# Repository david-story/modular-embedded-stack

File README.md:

# modular-embedded-stack

Credit card sized modular embedded stackable boards that was designed for fun for a microprocessor / 
microcontroller class. Base board is a microcontroller board that supports a thru-hole or smd PIC18F45K20 chip,
depending on which board you select. Daughter boards that are currently implemented have sensors and peripheals
that the user can interact with. 

The following is current included in the files:
- Board and schematic for thru-hole microcontroller
- Board and schematic for SMD microcontroller
- Board and schematic sensor daughter board

The following will be created in the future:
- Board and schematic for communication daughter board
- Other daughter boards and modules.

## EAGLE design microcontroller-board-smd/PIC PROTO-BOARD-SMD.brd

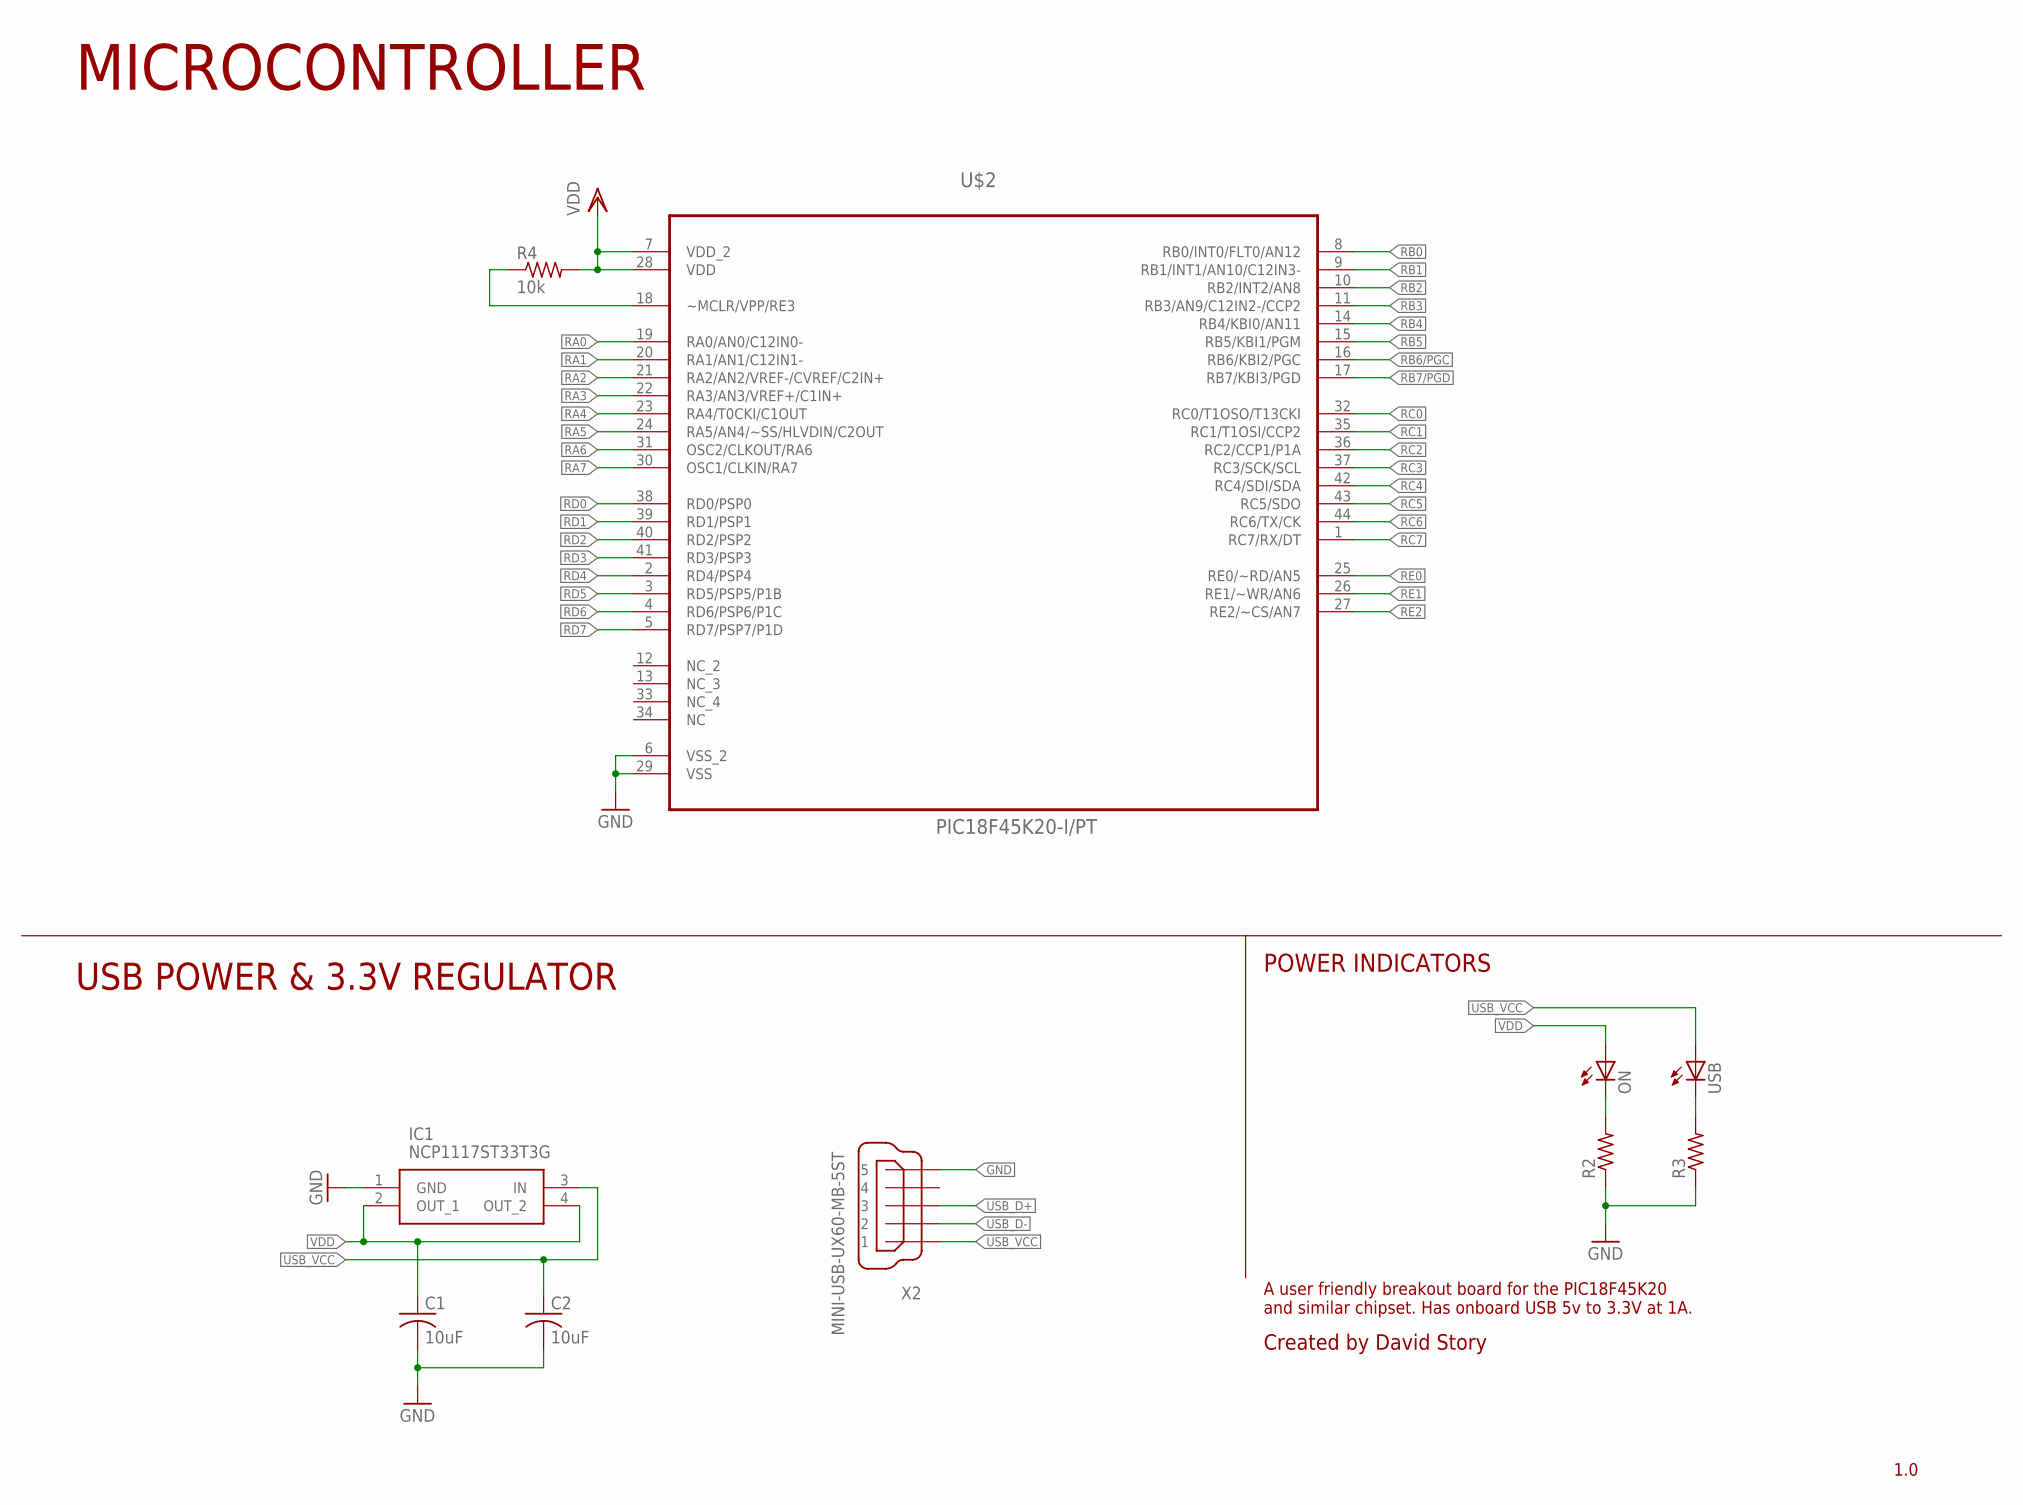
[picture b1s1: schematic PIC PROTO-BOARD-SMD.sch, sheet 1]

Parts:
C1, C2: 10uF; C0805
IC1: NCP1117ST33T3G; SOT230P700X180-4N
ON: LEDCHIP-LED0603; CHIP-LED0603
R2, R3: R-US_R0603; R0603
R4: 10k; R0805
U$2: PIC18F45K20-I/PT; QFP80P1200X1200X120-44N
USB: LEDCHIP-LED0603; CHIP-LED0603
X2: MINI-USB-UX60-MB-5ST; UX60-MB-5ST

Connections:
GND: C1.2, C2.2, IC1.1 (GND), R2.1, R3.1, U$2.6 (VSS_2), U$2.29 (VSS), X2.5; also elsewhere on the board
MCLR: R4.1, U$2.18 (~MCLR/VPP/RE3); also elsewhere on the board
ON_CATHODE: ON.C, R2.2
RA0: U$2.19 (RA0/AN0/C12IN0-); also elsewhere on the board
RA1: U$2.20 (RA1/AN1/C12IN1-); also elsewhere on the board
RA2: U$2.21 (RA2/AN2/VREF-/CVREF/C2IN+); also elsewhere on the board
RA3: U$2.22 (RA3/AN3/VREF+/C1IN+); also elsewhere on the board
RA4: U$2.23 (RA4/T0CKI/C1OUT); also elsewhere on the board
RA5: U$2.24 (RA5/AN4/~SS/HLVDIN/C2OUT); also elsewhere on the board
RA6: U$2.31 (OSC2/CLKOUT/RA6); also elsewhere on the board
RA7: U$2.30 (OSC1/CLKIN/RA7); also elsewhere on the board
RB0: U$2.8 (RB0/INT0/FLT0/AN12); also elsewhere on the board
RB1: U$2.9 (RB1/INT1/AN10/C12IN3-); also elsewhere on the board
RB2: U$2.10 (RB2/INT2/AN8); also elsewhere on the board
RB3: U$2.11 (RB3/AN9/C12IN2-/CCP2); also elsewhere on the board
RB4: U$2.14 (RB4/KBI0/AN11); also elsewhere on the board
RB5: U$2.15 (RB5/KBI1/PGM); also elsewhere on the board
RB6/PGC: U$2.16 (RB6/KBI2/PGC); also elsewhere on the board
RB7/PGD: U$2.17 (RB7/KBI3/PGD); also elsewhere on the board
RC0: U$2.32 (RC0/T1OSO/T13CKI); also elsewhere on the board
RC1: U$2.35 (RC1/T1OSI/CCP2); also elsewhere on the board
RC2: U$2.36 (RC2/CCP1/P1A); also elsewhere on the board
RC3: U$2.37 (RC3/SCK/SCL); also elsewhere on the board
RC4: U$2.42 (RC4/SDI/SDA); also elsewhere on the board
RC5: U$2.43 (RC5/SDO); also elsewhere on the board
RC6: U$2.44 (RC6/TX/CK); also elsewhere on the board
RC7: U$2.1 (RC7/RX/DT); also elsewhere on the board
RD0: U$2.38 (RD0/PSP0); also elsewhere on the board
RD1: U$2.39 (RD1/PSP1); also elsewhere on the board
RD2: U$2.40 (RD2/PSP2); also elsewhere on the board
RD3: U$2.41 (RD3/PSP3); also elsewhere on the board
RD4: U$2.2 (RD4/PSP4); also elsewhere on the board
RD5: U$2.3 (RD5/PSP5/P1B); also elsewhere on the board
RD6: U$2.4 (RD6/PSP6/P1C); also elsewhere on the board
RD7: U$2.5 (RD7/PSP7/P1D); also elsewhere on the board
RE0: U$2.25 (RE0/~RD/AN5); also elsewhere on the board
RE1: U$2.26 (RE1/~WR/AN6); also elsewhere on the board
RE2: U$2.27 (RE2/~CS/AN7); also elsewhere on the board
USB_CATHODE: R3.2, USB.C
USB_D+: X2.3; also elsewhere on the board
USB_D-: X2.2; also elsewhere on the board
USB_VCC: C2.1, IC1.3 (IN), USB.A, X2.1; also elsewhere on the board
VDD: C1.1, IC1.2 (OUT_1), IC1.4 (OUT_2), ON.A, R4.2, U$2.7 (VDD_2), U$2.28 (VDD); also elsewhere on the board

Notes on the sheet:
Created by David Story
1.0
MICROCONTROLLER
USB POWER & 3.3V REGULATOR
POWER INDICATORS
A user friendly breakout board for the PIC18F45K20 and similar chipset. Has onboard USB 5v to 3.3V at 1A.

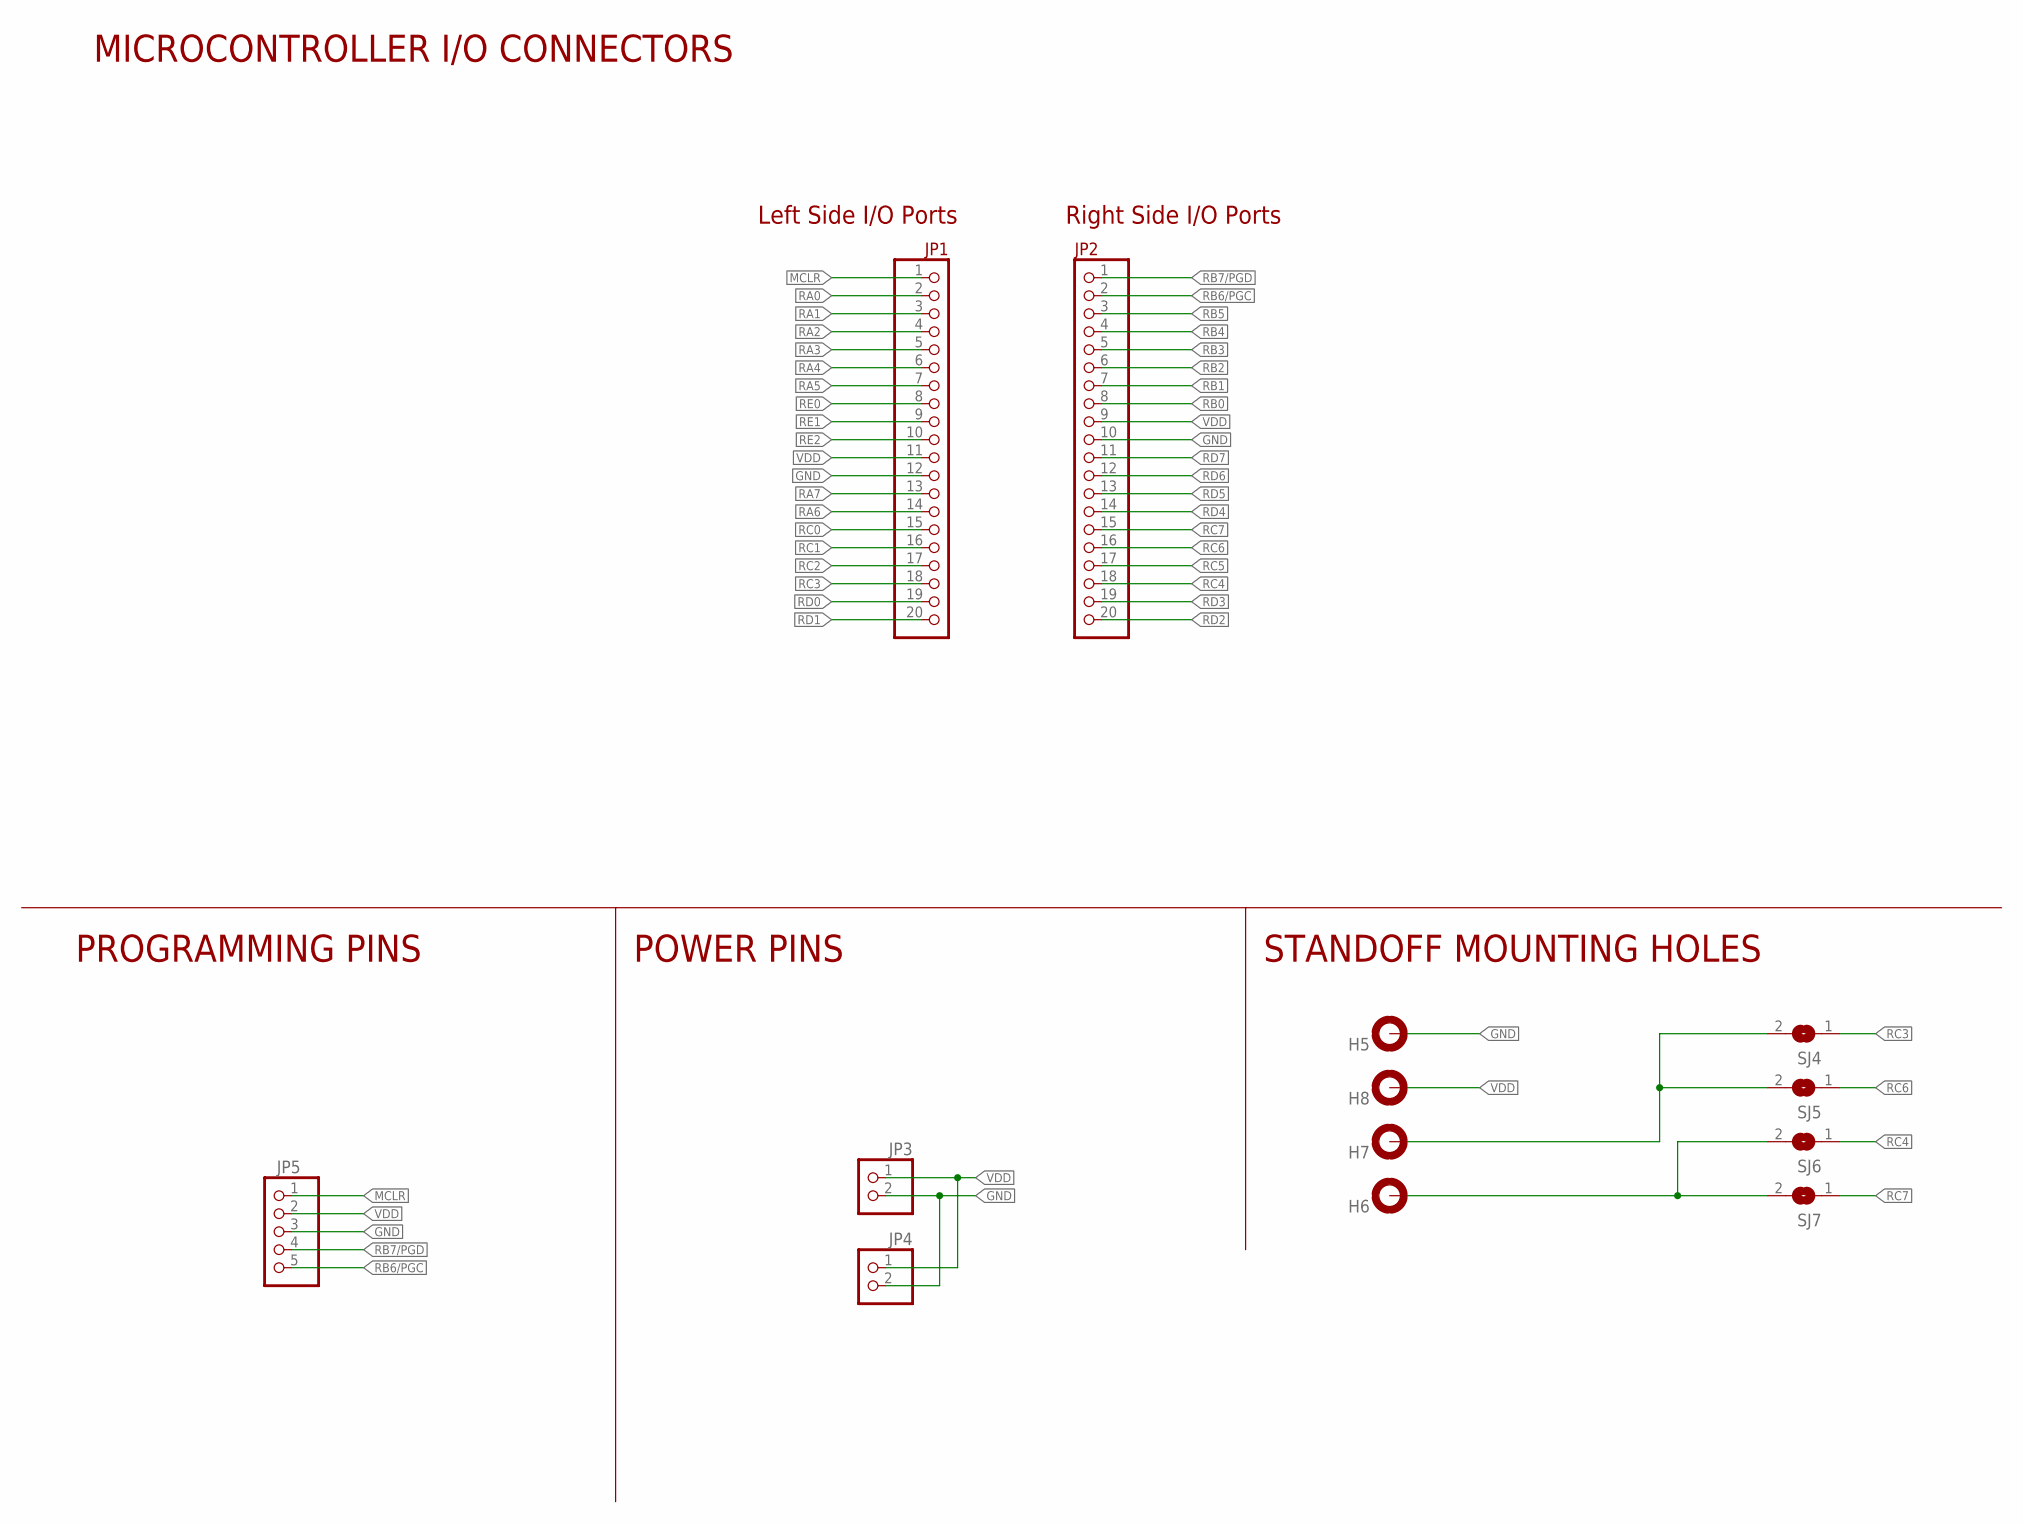
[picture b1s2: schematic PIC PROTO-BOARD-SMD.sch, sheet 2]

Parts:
H5, H6, H7, H8: MOUNT-PAD-ROUND3.3; 3,3-PAD
JP1, JP2: PINHD-1X20; 1X20
JP3, JP4: PINHD-1X2; 1X02
JP5: PINHD-1X5; 1X05
SJ4, SJ5, SJ6, SJ7: SJ

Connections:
COM_HOLE_1: H7.B3,3, SJ4.2, SJ5.2
COM_HOLE_2: H6.B3,3, SJ6.2, SJ7.2
GND: H5.B3,3, JP1.12, JP2.10, JP3.2, JP4.2, JP5.3; also elsewhere on the board
MCLR: JP1.1, JP5.1; also elsewhere on the board
RA0: JP1.2; also elsewhere on the board
RA1: JP1.3; also elsewhere on the board
RA2: JP1.4; also elsewhere on the board
RA3: JP1.5; also elsewhere on the board
RA4: JP1.6; also elsewhere on the board
RA5: JP1.7; also elsewhere on the board
RA6: JP1.14; also elsewhere on the board
RA7: JP1.13; also elsewhere on the board
RB0: JP2.8; also elsewhere on the board
RB1: JP2.7; also elsewhere on the board
RB2: JP2.6; also elsewhere on the board
RB3: JP2.5; also elsewhere on the board
RB4: JP2.4; also elsewhere on the board
RB5: JP2.3; also elsewhere on the board
RB6/PGC: JP2.2, JP5.5; also elsewhere on the board
RB7/PGD: JP2.1, JP5.4; also elsewhere on the board
RC0: JP1.15; also elsewhere on the board
RC1: JP1.16; also elsewhere on the board
RC2: JP1.17; also elsewhere on the board
RC3: JP1.18, SJ4.1; also elsewhere on the board
RC4: JP2.18, SJ6.1; also elsewhere on the board
RC5: JP2.17; also elsewhere on the board
RC6: JP2.16, SJ5.1; also elsewhere on the board
RC7: JP2.15, SJ7.1; also elsewhere on the board
RD0: JP1.19; also elsewhere on the board
RD1: JP1.20; also elsewhere on the board
RD2: JP2.20; also elsewhere on the board
RD3: JP2.19; also elsewhere on the board
RD4: JP2.14; also elsewhere on the board
RD5: JP2.13; also elsewhere on the board
RD6: JP2.12; also elsewhere on the board
RD7: JP2.11; also elsewhere on the board
RE0: JP1.8; also elsewhere on the board
RE1: JP1.9; also elsewhere on the board
RE2: JP1.10; also elsewhere on the board
VDD: H8.B3,3, JP1.11, JP2.9, JP3.1, JP4.1, JP5.2; also elsewhere on the board

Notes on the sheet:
Left Side I/O Ports
Right Side I/O Ports
PROGRAMMING PINS
POWER PINS
STANDOFF MOUNTING HOLES
MICROCONTROLLER I/O CONNECTORS

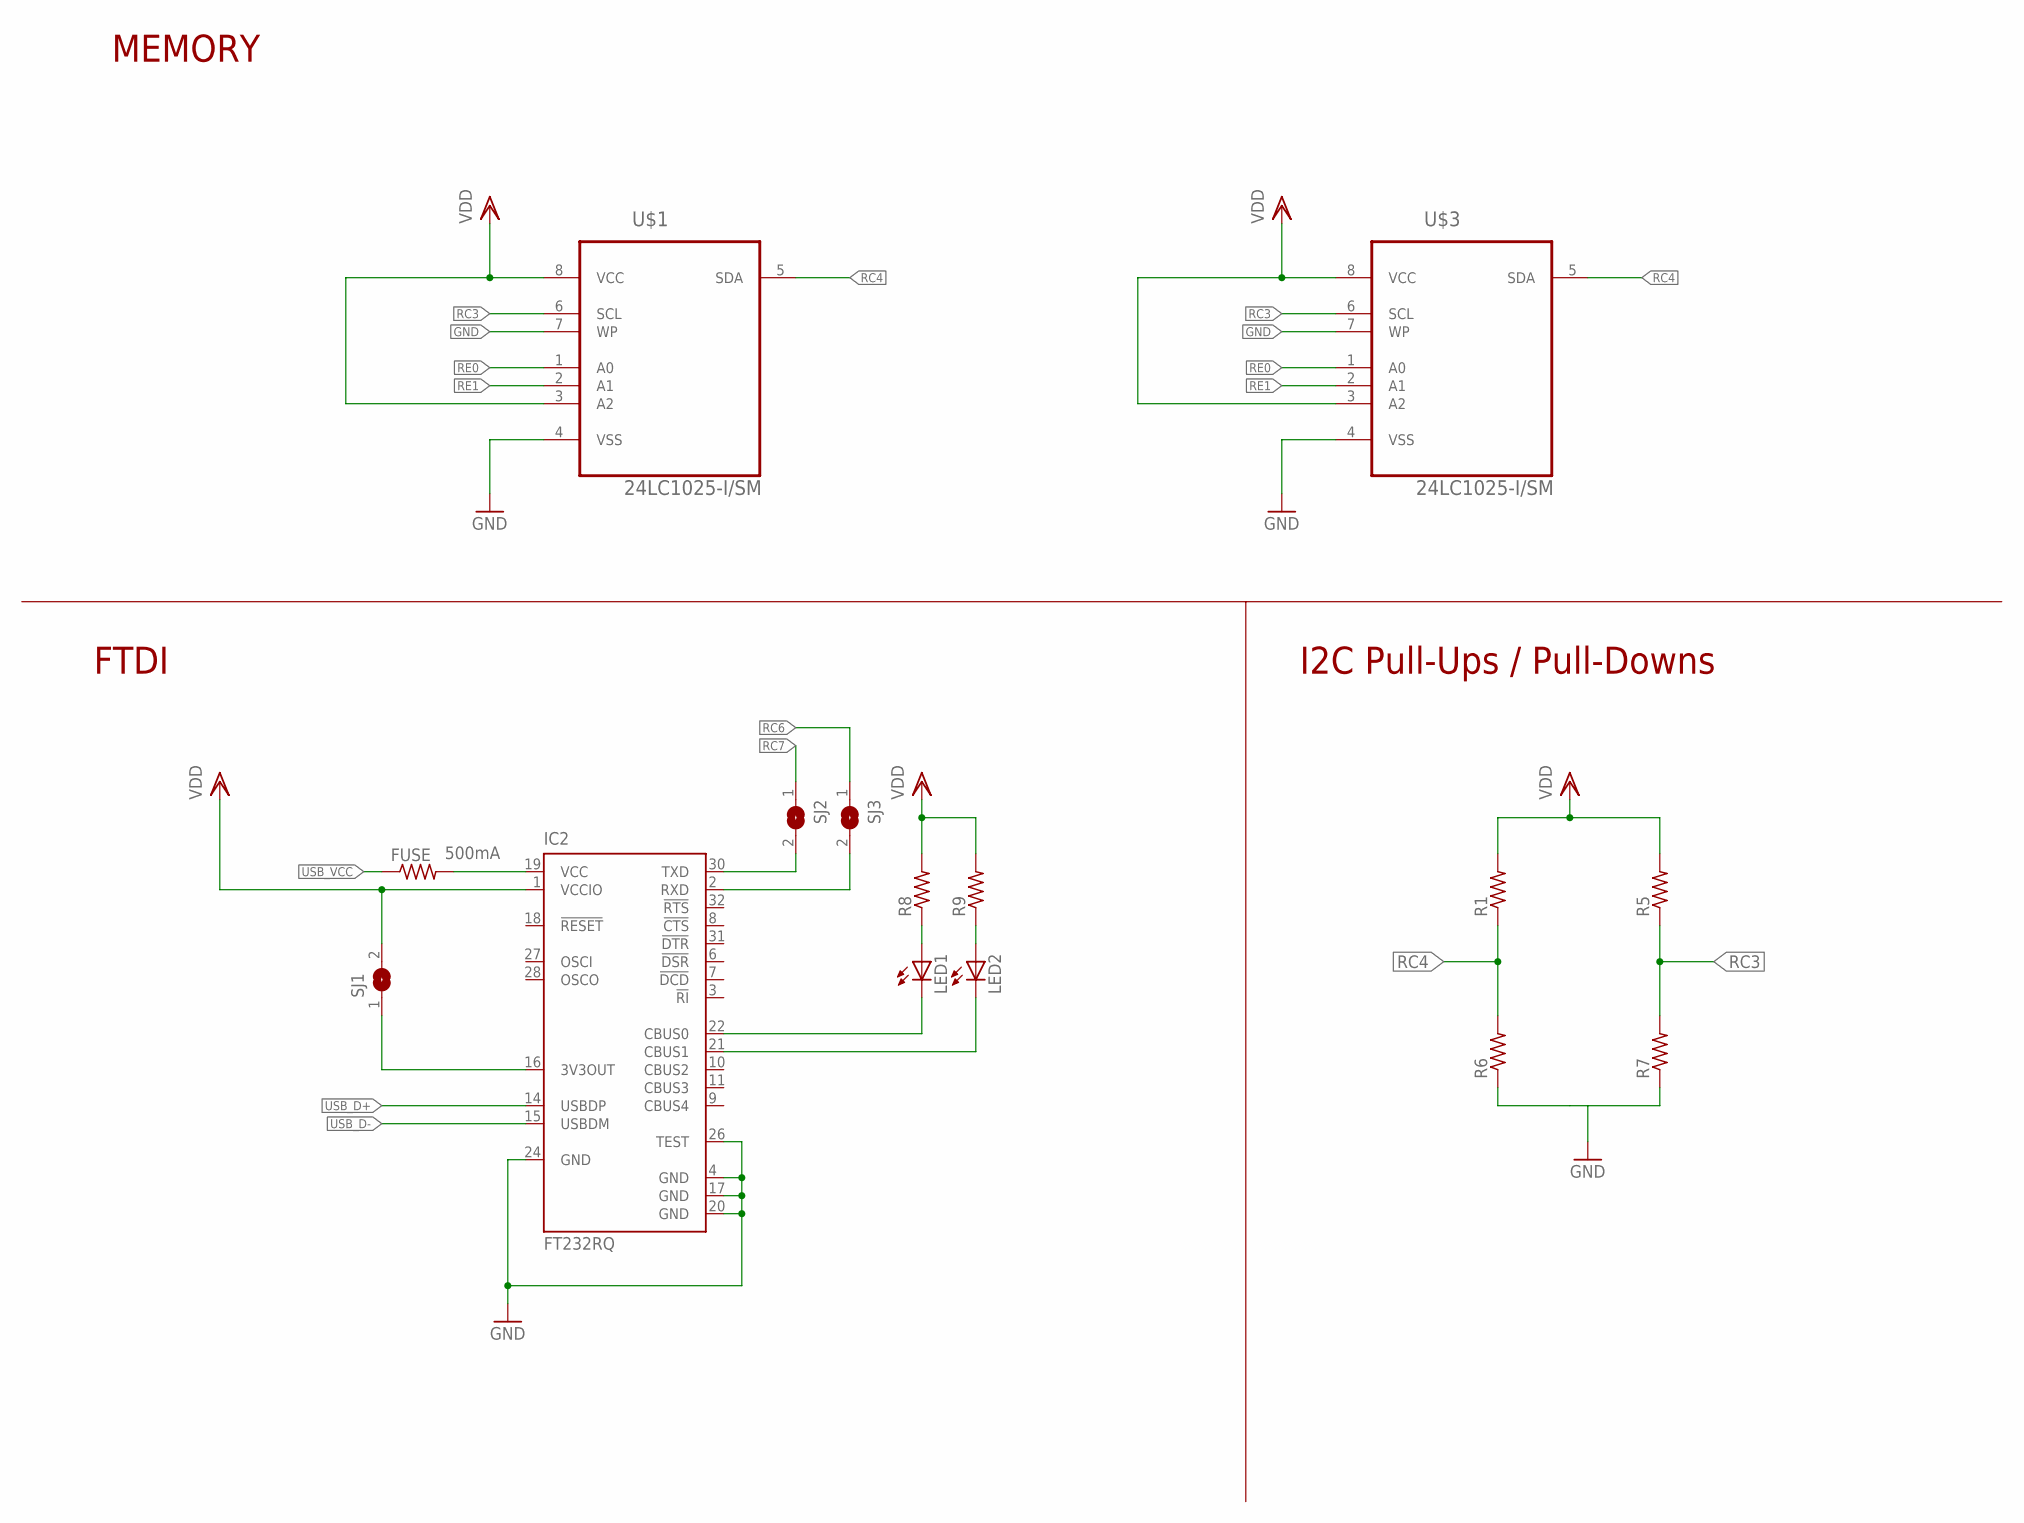
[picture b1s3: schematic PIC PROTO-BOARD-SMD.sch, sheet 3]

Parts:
FUSE: 500mA; M0805
IC2: FT232RQ; QFN32
LED1, LED2: LEDSML0603; SML0603
R1, R5, R6, R7, R8, R9: R-US_R0805; R0805
SJ1, SJ2, SJ3: SJ
U$1, U$3: 24LC1025-I/SM; SOIC127P794X203-8N

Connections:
3V3OUT: IC2.16 (3V3OUT), SJ1.1
FUSE_TO_FTDI: FUSE.2, IC2.19 (VCC)
GND: IC2.4 (GND), IC2.17 (GND), IC2.20 (GND), IC2.24 (GND), IC2.26 (TEST), R6.1, R7.1, U$1.4 (VSS), U$1.7 (WP), U$3.4 (VSS), U$3.7 (WP); also elsewhere on the board
LEDTX: LED1.A, R8.1
RC3: R5.1, R7.2, U$1.6 (SCL), U$3.6 (SCL); also elsewhere on the board
RC4: R1.1, R6.2, U$1.5 (SDA), U$3.5 (SDA); also elsewhere on the board
RC6: SJ3.1; also elsewhere on the board
RC7: SJ2.1; also elsewhere on the board
RE0: U$1.1 (A0), U$3.1 (A0); also elsewhere on the board
RE1: U$1.2 (A1), U$3.2 (A1); also elsewhere on the board
RXD: IC2.2 (RXD), SJ3.2
RXLED: LED2.A, R9.1
RX_LED: IC2.21 (CBUS1), LED2.C
TXD: IC2.30 (TXD), SJ2.2
TX_LED: IC2.22 (CBUS0), LED1.C
USB_D+: IC2.14 (USBDP); also elsewhere on the board
USB_D-: IC2.15 (USBDM); also elsewhere on the board
USB_VCC: FUSE.1; also elsewhere on the board
VDD: IC2.1 (VCCIO), R1.2, R5.2, R8.2, R9.2, SJ1.2, U$1.3 (A2), U$1.8 (VCC), U$3.3 (A2), U$3.8 (VCC); also elsewhere on the board

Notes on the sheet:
MEMORY
I2C Pull-Ups / Pull-Downs
FTDI

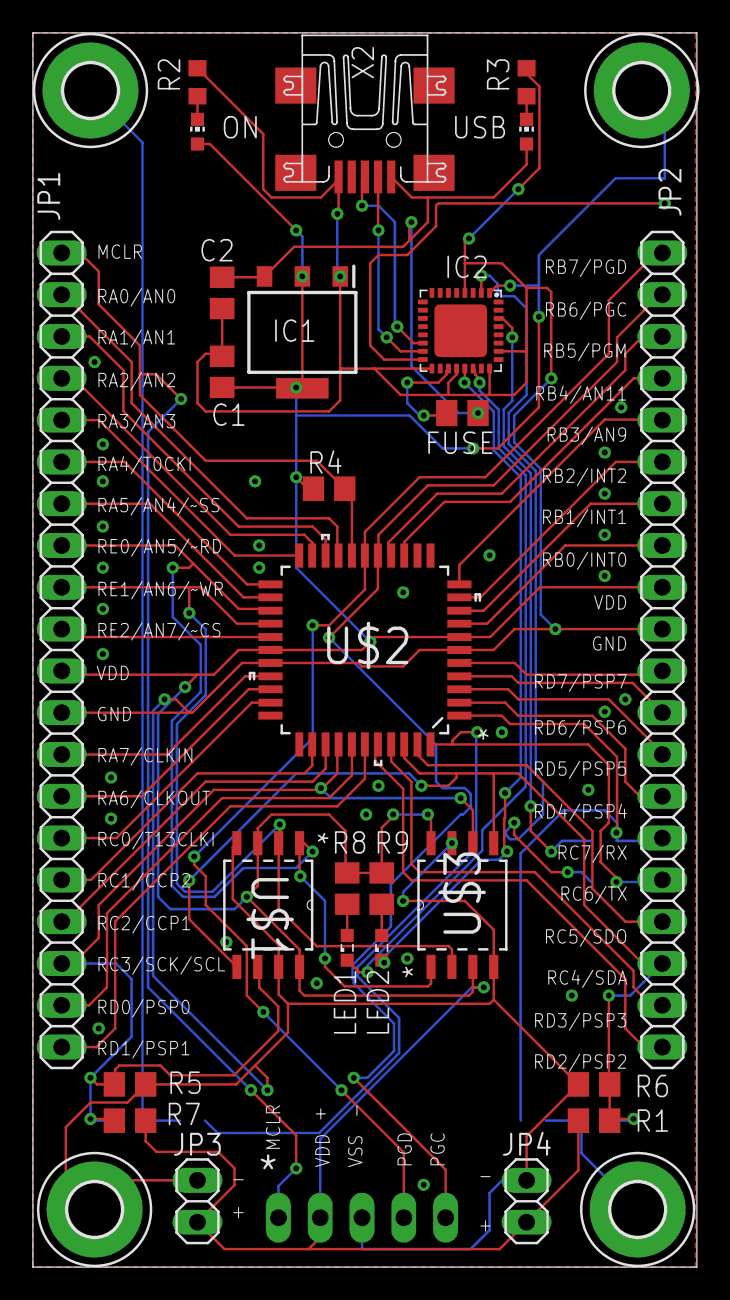
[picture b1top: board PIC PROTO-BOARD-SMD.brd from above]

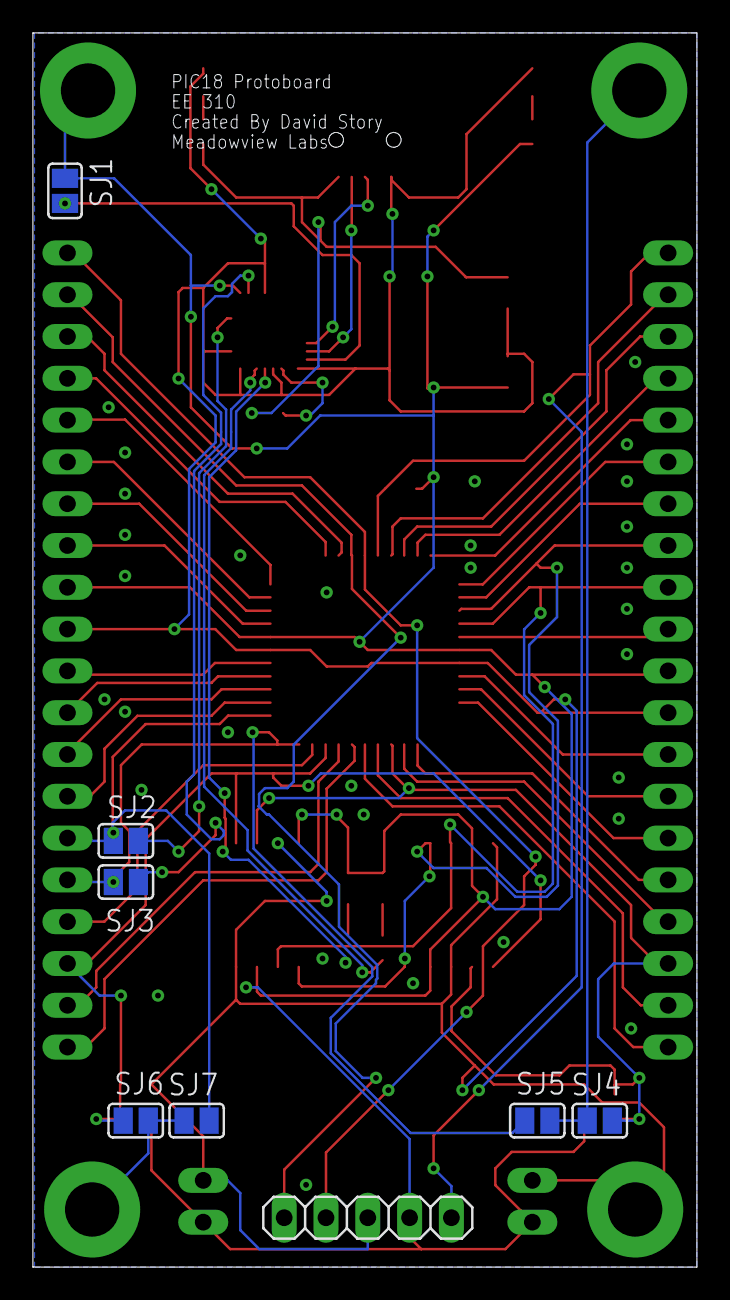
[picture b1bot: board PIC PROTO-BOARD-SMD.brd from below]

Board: 2 copper layers, 40.4 x 75.0 mm, 38 parts (8 on the bottom side), 53 nets.

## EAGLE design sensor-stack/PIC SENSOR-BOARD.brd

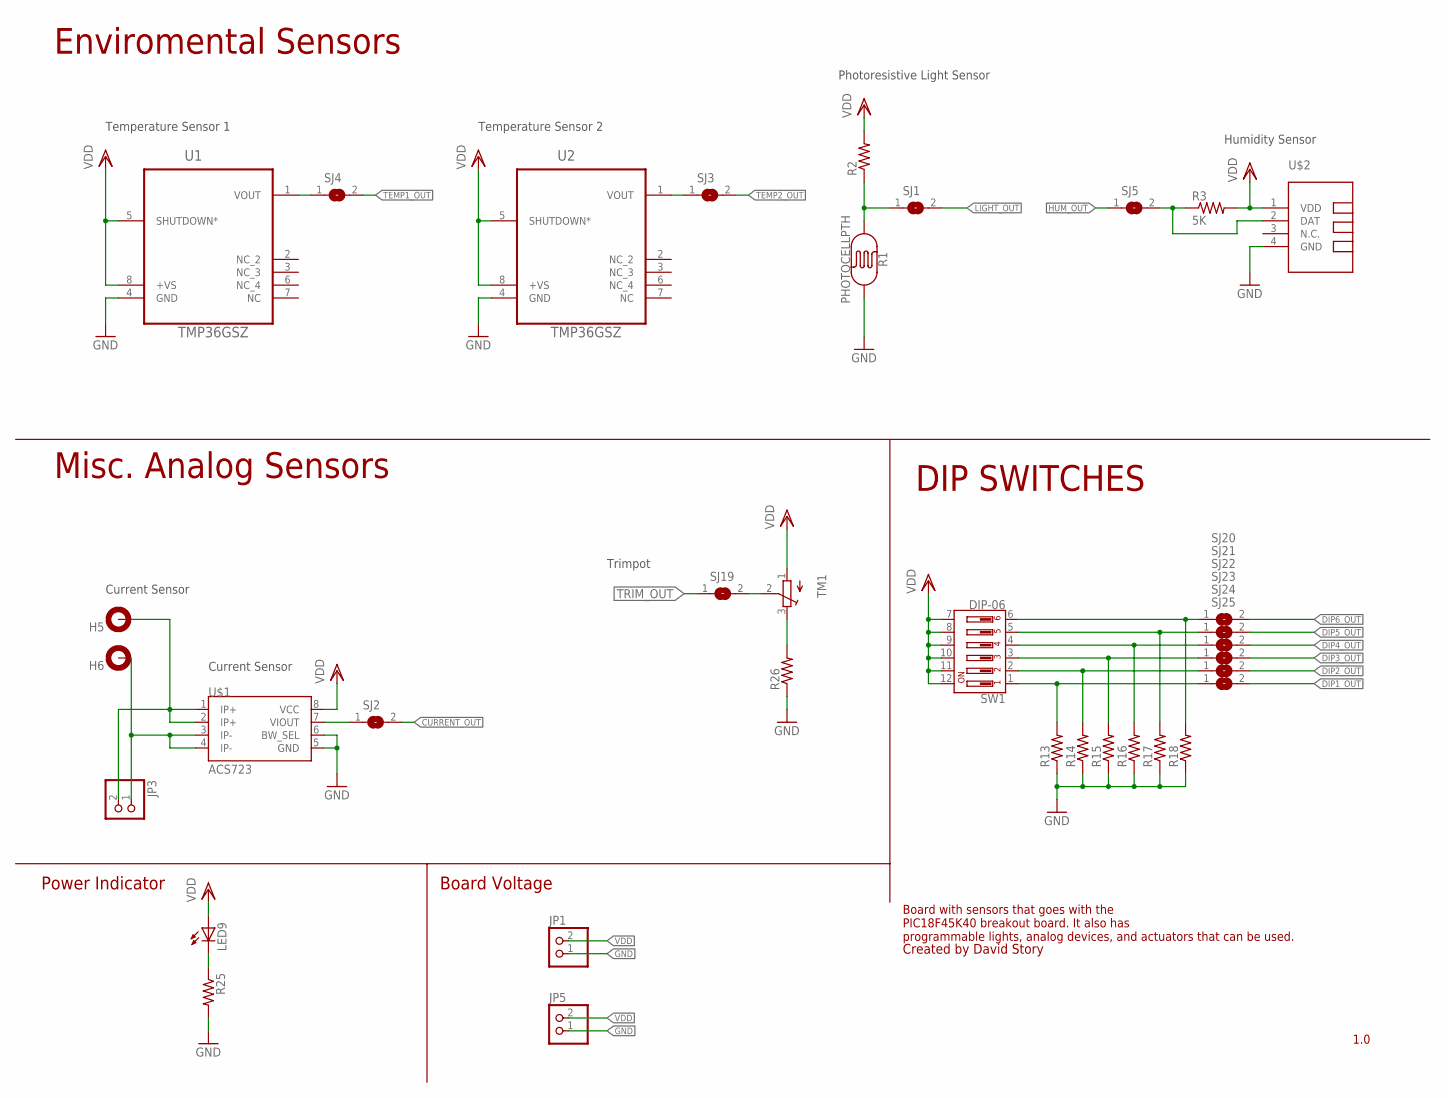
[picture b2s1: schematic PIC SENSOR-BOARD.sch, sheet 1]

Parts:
H5, H6: MOUNT-PAD-ROUND3.3; 3,3-PAD
JP1, JP3, JP5: PINHD-1X2; 1X02
LED9: LEDCHIPLED_0603; CHIPLED_0603
R1: PHOTOCELLPTH; PHOTOCELL
R2, R25, R26: R-US_M0805; M0805
R3: 5K; M0805
R13, R14, R15, R16, R17, R18: R-US_R0805; R0805
SJ1, SJ2, SJ3, SJ4, SJ5, SJ19, SJ20, SJ21, SJ22, SJ23, SJ24, SJ25: SJ
SW1: DIP-06; DIPSWITCH-06-SMD
TM1: TRIMPOT3386; TRIM-3386
U1, U2: TMP36GSZ; SOIC127P600X175-8N
U$1: ACS723; SO08
U$2: TEMP-HUM-SENSOR-DHT11

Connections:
CURRENT_LINE: SJ2.1, U$1.7 (VIOUT)
CURRENT_OUT: SJ2.2; also elsewhere on the board
DIP1_LINE: R13.2, SJ25.1, SW1.1
DIP1_OUT: SJ25.2; also elsewhere on the board
DIP2_LINE: R14.2, SJ24.1, SW1.2
DIP2_OUT: SJ24.2; also elsewhere on the board
DIP3_LINE: R15.2, SJ23.1, SW1.3
DIP3_OUT: SJ23.2; also elsewhere on the board
DIP4_LINE: R16.2, SJ22.1, SW1.4
DIP4_OUT: SJ22.2; also elsewhere on the board
DIP5_LINE: R17.2, SJ21.1, SW1.5
DIP5_OUT: SJ21.2; also elsewhere on the board
DIP6_LINE: R18.2, SJ20.1, SW1.6
DIP6_OUT: SJ20.2; also elsewhere on the board
GND: JP1.1, JP5.1, R1.2, R13.1, R14.1, R15.1, R16.1, R17.1, R18.1, R25.2, R26.1, U1.4 (GND), U2.4 (GND), U$1.5 (GND), U$1.6 (BW_SEL), U$2.4 (GND); also elsewhere on the board
HUM_DATA: R3.1, SJ5.2, U$2.2 (DAT)
HUM_OUT: SJ5.1; also elsewhere on the board
IP+: H5.B3,3, JP3.2, U$1.1 (IP+), U$1.2 (IP+)
IP-: H6.B3,3, JP3.1, U$1.3 (IP-), U$1.4 (IP-)
LIGHT_LINE: R1.1, R2.1, SJ1.1
LIGHT_OUT: SJ1.2; also elsewhere on the board
POWER-: LED9.C, R25.1
T1_LINE: SJ4.1, U1.1 (VOUT)
T2_LINE: SJ3.1, U2.1 (VOUT)
TEMP1_OUT: SJ4.2; also elsewhere on the board
TEMP2_OUT: SJ3.2; also elsewhere on the board
TRIM: R26.2, TM1.3 (E)
TRIM_JUMP: SJ19.2, TM1.2 (S)
TRIM_OUT: SJ19.1; also elsewhere on the board
VDD: JP1.2, JP5.2, LED9.A, R2.2, R3.2, SW1.7, SW1.8, SW1.9, SW1.10, SW1.11, SW1.12, TM1.1 (A), U1.5 (SHUTDOWN*), U1.8 (+VS), U2.5 (SHUTDOWN*), U2.8 (+VS), U$1.8 (VCC), U$2.1 (VDD); also elsewhere on the board

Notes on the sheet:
Created by David Story
1.0
Board with sensors that goes with the PIC18F45K40 breakout board. It also has programmable lights, analog devices, and actuators that can be used.
Misc. Analog Sensors
Enviromental Sensors
DIP SWITCHES
Temperature Sensor 1
Temperature Sensor 2
Photoresistive Light Sensor
Humidity Sensor
Current Sensor
Trimpot
Power Indicator
Board Voltage

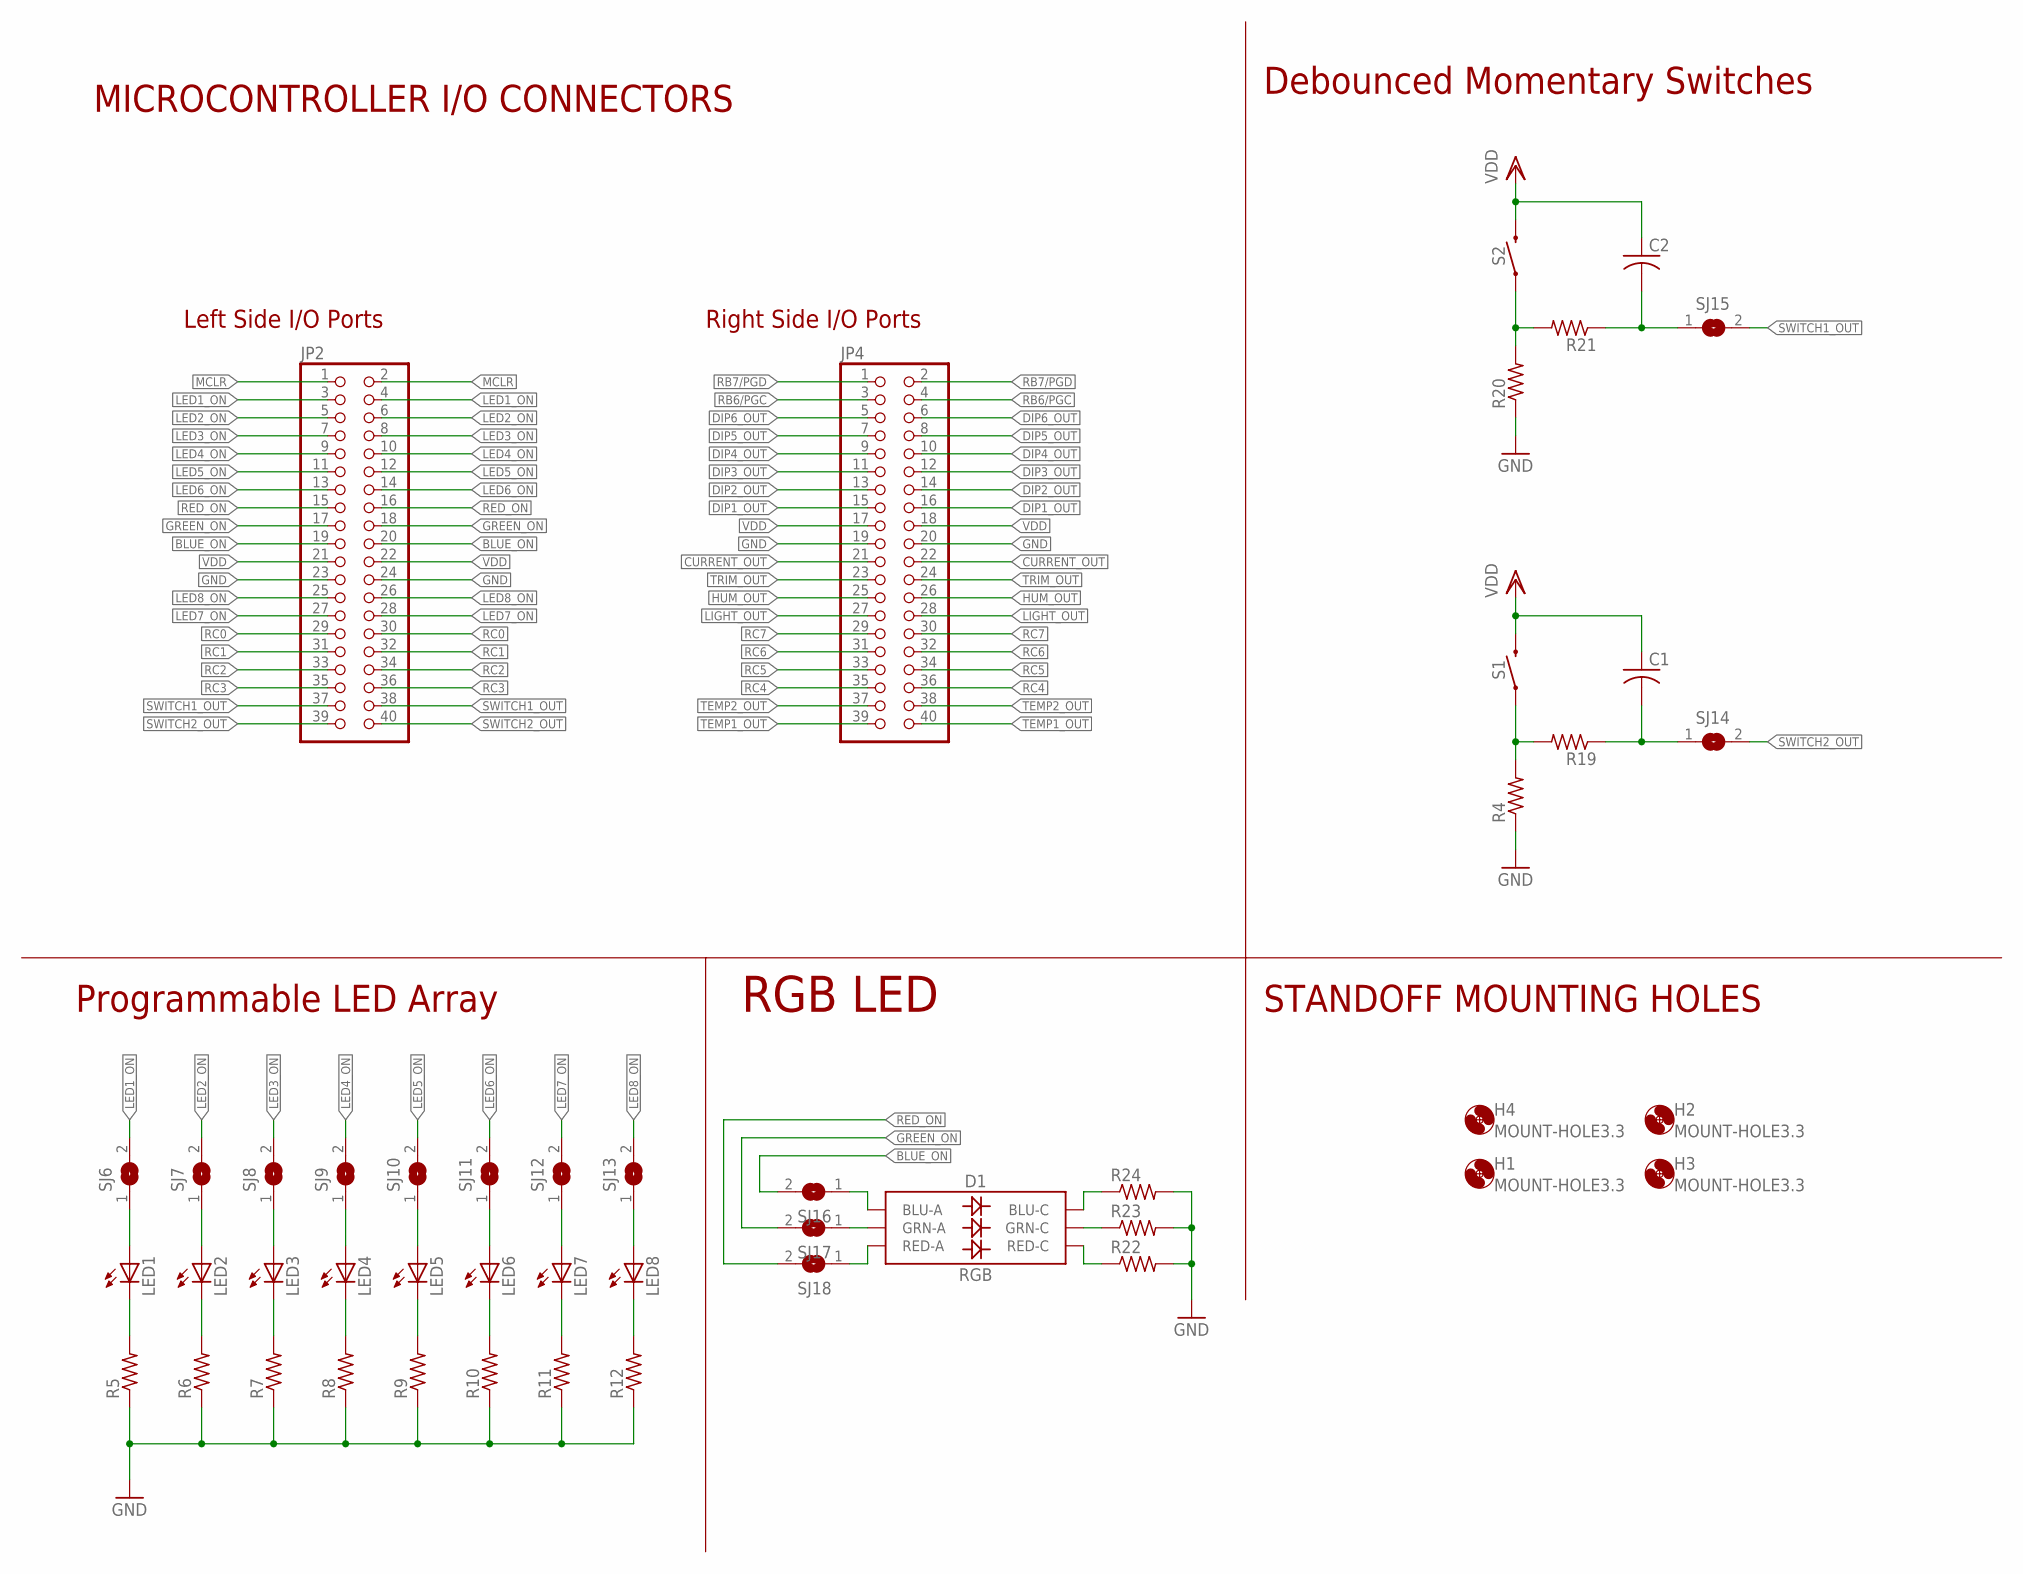
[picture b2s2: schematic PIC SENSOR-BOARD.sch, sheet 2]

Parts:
C1, C2: C-USC0805; C0805
D1: RGB; PLCC-6-LED
H1, H2, H3, H4: MOUNT-HOLE3.3; 3,3
JP2, JP4: PINHD-2X20; 2X20
LED1, LED2, LED3, LED4, LED5, LED6, LED7, LED8: LEDSML0603; SML0603
R4, R5, R6, R7, R8, R9, R10, R11, R12, R19, R20, R21: R-US_M0805; M0805
R22, R23, R24: R-US_R0805; R0805
S1, S2: MOMENTARY-SWITCH-SPST-PTH-6.0MM; TACTILE_SWITCH_PTH_6.0MM
SJ6, SJ7, SJ8, SJ9, SJ10, SJ11, SJ12, SJ13, SJ14, SJ15, SJ16, SJ17, SJ18: SJ

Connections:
BLUE+: D1.AB (BLU-A), SJ16.1
BLUE-: D1.CB (BLU-C), R24.1
BLUE_ON: JP2.19, JP2.20, SJ16.2
CAP2_NEG: C1.2, R19.1, SJ14.1
CAP_NEG: C2.2, R21.1, SJ15.1
CURRENT_OUT: JP4.21, JP4.22; also elsewhere on the board
DIP1_OUT: JP4.15, JP4.16; also elsewhere on the board
DIP2_OUT: JP4.13, JP4.14; also elsewhere on the board
DIP3_OUT: JP4.11, JP4.12; also elsewhere on the board
DIP4_OUT: JP4.9, JP4.10; also elsewhere on the board
DIP5_OUT: JP4.7, JP4.8; also elsewhere on the board
DIP6_OUT: JP4.5, JP4.6; also elsewhere on the board
GND: JP2.23, JP2.24, JP4.19, JP4.20, R4.1, R5.1, R6.1, R7.1, R8.1, R9.1, R10.1, R11.1, R12.1, R20.1, R22.2, R23.2, R24.2; also elsewhere on the board
GREEN+: D1.AG (GRN-A), SJ17.1
GREEN-: D1.CG (GRN-C), R23.1
GREEN_ON: JP2.17, JP2.18, SJ17.2
HUM_OUT: JP4.25, JP4.26; also elsewhere on the board
L1+: LED1.A, SJ6.1
L1-: LED1.C, R5.2
L2+: LED2.A, SJ7.1
L2-: LED2.C, R6.2
L3+: LED3.A, SJ8.1
L3-: LED3.C, R7.2
L4+: LED4.A, SJ9.1
L4-: LED4.C, R8.2
L5+: LED5.A, SJ10.1
L5-: LED5.C, R9.2
L6+: LED6.A, SJ11.1
L6-: LED6.C, R10.2
L7+: LED7.A, SJ12.1
L7-: LED7.C, R11.2
L8+: LED8.A, SJ13.1
L8-: LED8.C, R12.2
LED1_ON: JP2.3, JP2.4, SJ6.2
LED2_ON: JP2.5, JP2.6, SJ7.2
LED3_ON: JP2.7, JP2.8, SJ8.2
LED4_ON: JP2.9, JP2.10, SJ9.2
LED5_ON: JP2.11, JP2.12, SJ10.2
LED6_ON: JP2.13, JP2.14, SJ11.2
LED7_ON: JP2.27, JP2.28, SJ12.2
LED8_ON: JP2.25, JP2.26, SJ13.2
LIGHT_OUT: JP4.27, JP4.28; also elsewhere on the board
MCLR: JP2.1, JP2.2
RB6/PGC: JP4.3, JP4.4
RB7/PGD: JP4.1, JP4.2
RC0: JP2.29, JP2.30
RC1: JP2.31, JP2.32
RC2: JP2.33, JP2.34
RC3: JP2.35, JP2.36
RC4: JP4.35, JP4.36
RC5: JP4.33, JP4.34
RC6: JP4.31, JP4.32
RC7: JP4.29, JP4.30
RED+: D1.AR (RED-A), SJ18.1
RED-: D1.CR (RED-C), R22.1
RED_ON: JP2.15, JP2.16, SJ18.2
SWITCH1_OUT: JP2.37, JP2.38, SJ15.2
SWITCH2_OUT: JP2.39, JP2.40, SJ14.2
SW_NEG: R20.2, R21.2, S2.1
SW_NEG2: R4.2, R19.2, S1.1
TEMP1_OUT: JP4.39, JP4.40; also elsewhere on the board
TEMP2_OUT: JP4.37, JP4.38; also elsewhere on the board
TRIM_OUT: JP4.23, JP4.24; also elsewhere on the board
VDD: C1.1, C2.1, JP2.21, JP2.22, JP4.17, JP4.18, S1.3 (2), S2.3 (2); also elsewhere on the board

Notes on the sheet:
Left Side I/O Ports
Right Side I/O Ports
Programmable LED Array
STANDOFF MOUNTING HOLES
MICROCONTROLLER I/O CONNECTORS
Debounced Momentary Switches
RGB LED

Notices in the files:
parts and their libraries:
SparkFun-Sensors: Licensing: Creative Commons ShareAlike 4.0 International - https://creativecommons.org/licenses/by-sa/4.0
diy-modules: Released under the Creative Commons Attribution 4.0 International License: http://creativecommons.org/licenses/by/4.0
